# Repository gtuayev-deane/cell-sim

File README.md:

# Cell Simulator

This cell-sim is designed to mimic a LiPo battery pack for develpoment of the surrounding electronics, like a BMS.

- 16 channels
- Open-Source hardware design, you can embed onto your own HIL setup
- ⚡️ 0-4.5V and 0-500mA per channel
- DMM muxed to each channel for arbitarily precise measurment
- Open-circuit simulation on each channel
- 📏 16bit ADC feedback for voltage and current
- 🔌 USB w/ Python software interface (+ 100MBit Ethernet + WiFi waiting for firmware support)

## Design overview

## Getting Started

1. Install python if you don't have it already
2. Install the requirements `pip install -r requirements.txt`
3. Connect the board via USB

4. Power the board with the 12V input (supply: 1A minimum, 3A recommended)
5. Run the example python script `python example_set_voltages.py`
6. Voltages should be set to 3.5V, then rainbow from 1V to 4V across the 16 channels and current should be close to 0A.

You should see something like this:

## Notes
1. To get best low noise performance, use a quality power supply for the input supply.

## Firmware

### Update Firmware
We use PlatformIO to build and upload the firmware via USB.
1. Install PlatformIO: https://platformio.org/install
2. Connect the board via USB (might need to accept connection popup on Mac)
3. Run `pio run -t upload` or install the PlatformIO VSCode extension and use the upload button.

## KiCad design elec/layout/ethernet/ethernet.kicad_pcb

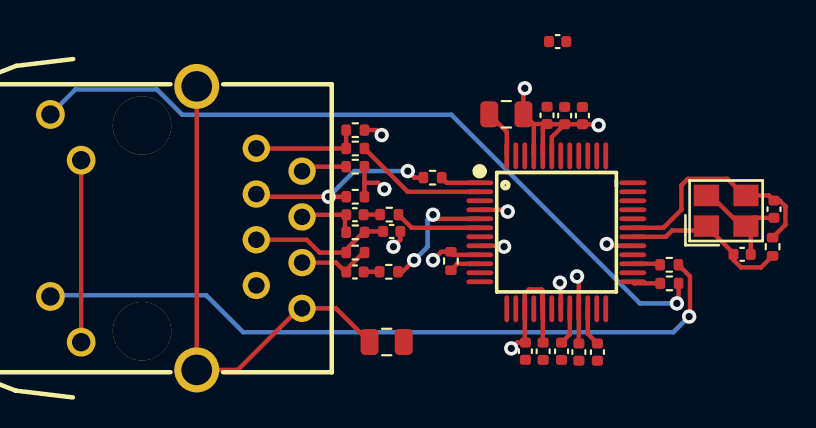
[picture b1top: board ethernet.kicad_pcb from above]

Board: 2 copper layers, 32 parts (0 on the bottom side), 27 nets.

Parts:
C1: 50V 1nF X7R ±10% 0805 Multilayer Ceramic Capacito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; C0805
C2: 50V 22nF X7R ±10% 0402 Multilayer Ceramic Capacit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; C0402
C3, C4: 50V 6.8nF X7R ±10% 0402 Multilayer Ceramic Capaci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; C0402
C5, C6: 50V 10nF X7R ±10% 0402 Multilayer Ceramic Capacit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; C0402
C7: 10V 4.7uF X5R ±20% 0402 Multilayer Ceramic Capaci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; C0402
C8, C9, C10, C11, C12, C13: 16V 100nF X7R ±10% 0402 Multilayer Ceramic Capaci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; C0402
C14: 25V 10uF X5R ±10% 0805 Multilayer Ceramic Capacit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; C0805
C15, C16: 50V 10pF C0G ±5% 0402 Multilayer Ceramic Capacito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; C0402
R1, R2: 62.5mW Thick Film Resistors 50V ±100ppm/℃ ±1% 200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; R0402
R3, R4, R8, R9: 62.5mW Thick Film Resistors 50V ±100ppm/℃ ±1% 33Ω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; R0402
R5, R6, R10, R11: 62.5mW Thick Film Resistors 50V ±100ppm/℃ ±1% 49.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; R0402
R7: 62.5mW Thick Film Resistors 50V ±1% ±200ppm/℃ 10Ω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; R0402
R12: 62.5mW Thick Film Resistors 50V ±100ppm/℃ ±1% 12.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; R0402
R13: 62.5mW Thick Film Resistors 50V ±100ppm/℃ ±1% 1MΩ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; R0402
U1: ?; LQFP-48_L7.0-W7.0-P0.50-LS9.0-BL
U2: ?; RJ45-TH_J1B1211CCD
U3: ?; CRYSTAL-SMD_4P-L3.2-W2.5-BL

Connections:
_1v2o: C6.1, U1.22
actled: R2.1, U1.27
cgnd: C1.1, U2.8, U2.13, U2.14
exres1: R12.1, U1.10
gnd-1: C1.2, C2.2, C5.2, C6.2, C7.2, C8.2, C9.2, C10.2, C11.2, C12.2, C13.2, C14.2, R12.2, U1.3, U1.9, U1.14, U1.16, U1.19, U1.29, U1.48
linkled: R1.1, U1.25
lled_minus: R1.2, U2.9
nc: U1.12, U1.13, U1.46, U1.47
oscillator-gnd: C15.2, C16.2, U3.2, U3.4
rct: C5.1, R10.2, R11.2, U2.5
rd_minus: C3.2, R10.1, U2.6
rd_plus: C4.2, R11.1, U2.4
rled_minus: R2.2, U2.11
rsvd: U1.23, U1.38, U1.39, U1.40, U1.41, U1.42
rx_minus_damping-vcc: C3.1, R8.2
rx_plus_damping-vcc: C4.1, R9.2
rxn: R8.1, U1.5
rxp: R9.1, U1.6
tct: C2.1, R7.2, U2.2
td_minus: R4.2, R6.2, U2.3
td_plus: R3.2, R5.2, U2.1
tocap: C7.1, U1.20
txn: R4.1, U1.1
txp: R3.1, U1.2
vcc: C8.1, C9.1, C10.1, C11.1, C12.1, C13.1, C14.1, R5.1, R6.1, R7.1, U1.4, U1.8, U1.11, U1.15, U1.17, U1.21, U1.28, U1.43, U1.44, U1.45, U2.10, U2.12
xi_slash_clkin: C15.1, R13.1, U1.30, U3.1
xo: C16.1, R13.2, U1.31, U3.3

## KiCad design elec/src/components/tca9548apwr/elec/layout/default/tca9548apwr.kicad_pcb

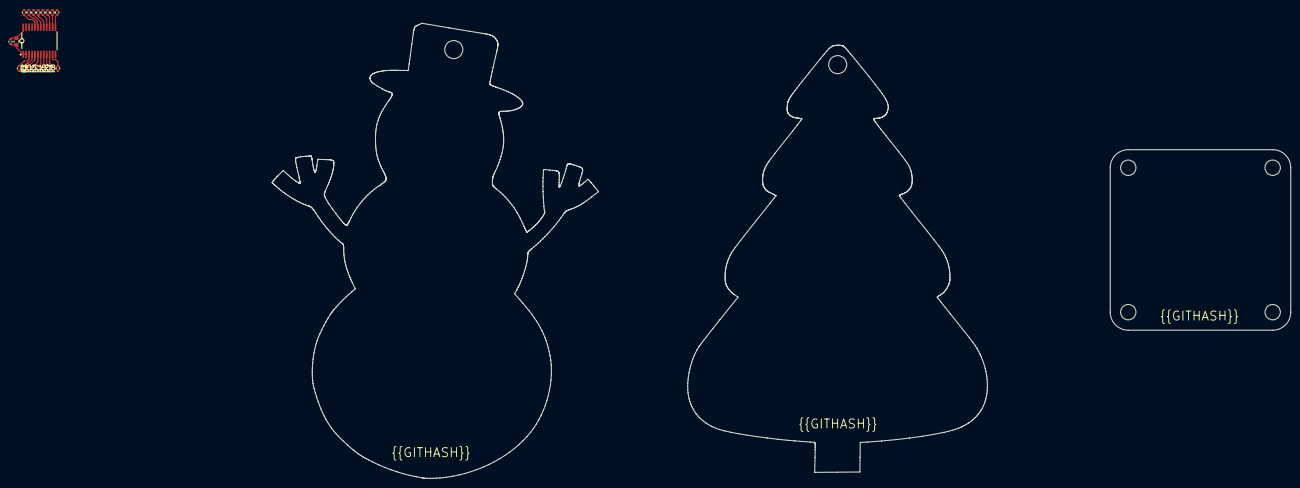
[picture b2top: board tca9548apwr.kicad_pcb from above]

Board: 2 copper layers, 20 parts (0 on the bottom side), 19 nets.

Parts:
C1: 16V 100nF X7R ±10% 0402 Multilayer Ceramic Capaci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; C0402
C2: 16V 2.2uF X5R ±10% 0603 Multilayer Ceramic Capaci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; C0603
R1, R2, R3, R4, R5, R6, R7, R8, R9, R10, R11, R12, R13, R14, R15, R16, R17: 62.5mW Thick Film Resistors 50V ±100ppm/℃ ±1% 10k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; R0402
U1: TSSOP-24_L7.8-W4.4-P0.65-LS6.4-BL

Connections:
ic-gnd: C1.2, C2.2, U1.1, U1.2, U1.12, U1.21
ic-scl: R2.2, U1.5
ic-scl-1: R4.2, U1.7
ic-scl-2: R6.2, U1.9
ic-scl-3: R8.2, U1.11
ic-scl-4: R10.2, U1.14
ic-scl-5: R12.2, U1.16
ic-scl-6: R14.2, U1.18
ic-scl-7: R16.2, U1.20
ic-sda: R3.2, U1.4
ic-sda-1: R5.2, U1.6
ic-sda-2: R7.2, U1.8
ic-sda-3: R9.2, U1.10
ic-sda-4: R11.2, U1.13
ic-sda-5: R13.2, U1.15
ic-sda-6: R15.2, U1.17
ic-sda-7: R17.2, U1.19
reset_: R1.1, U1.3
vcc: C1.1, C2.1, R1.2, R2.1, R3.1, R4.1, R5.1, R6.1, R7.1, R8.1, R9.1, R10.1, R11.1, R12.1, R13.1, R14.1, R15.1, R16.1, R17.1, U1.24

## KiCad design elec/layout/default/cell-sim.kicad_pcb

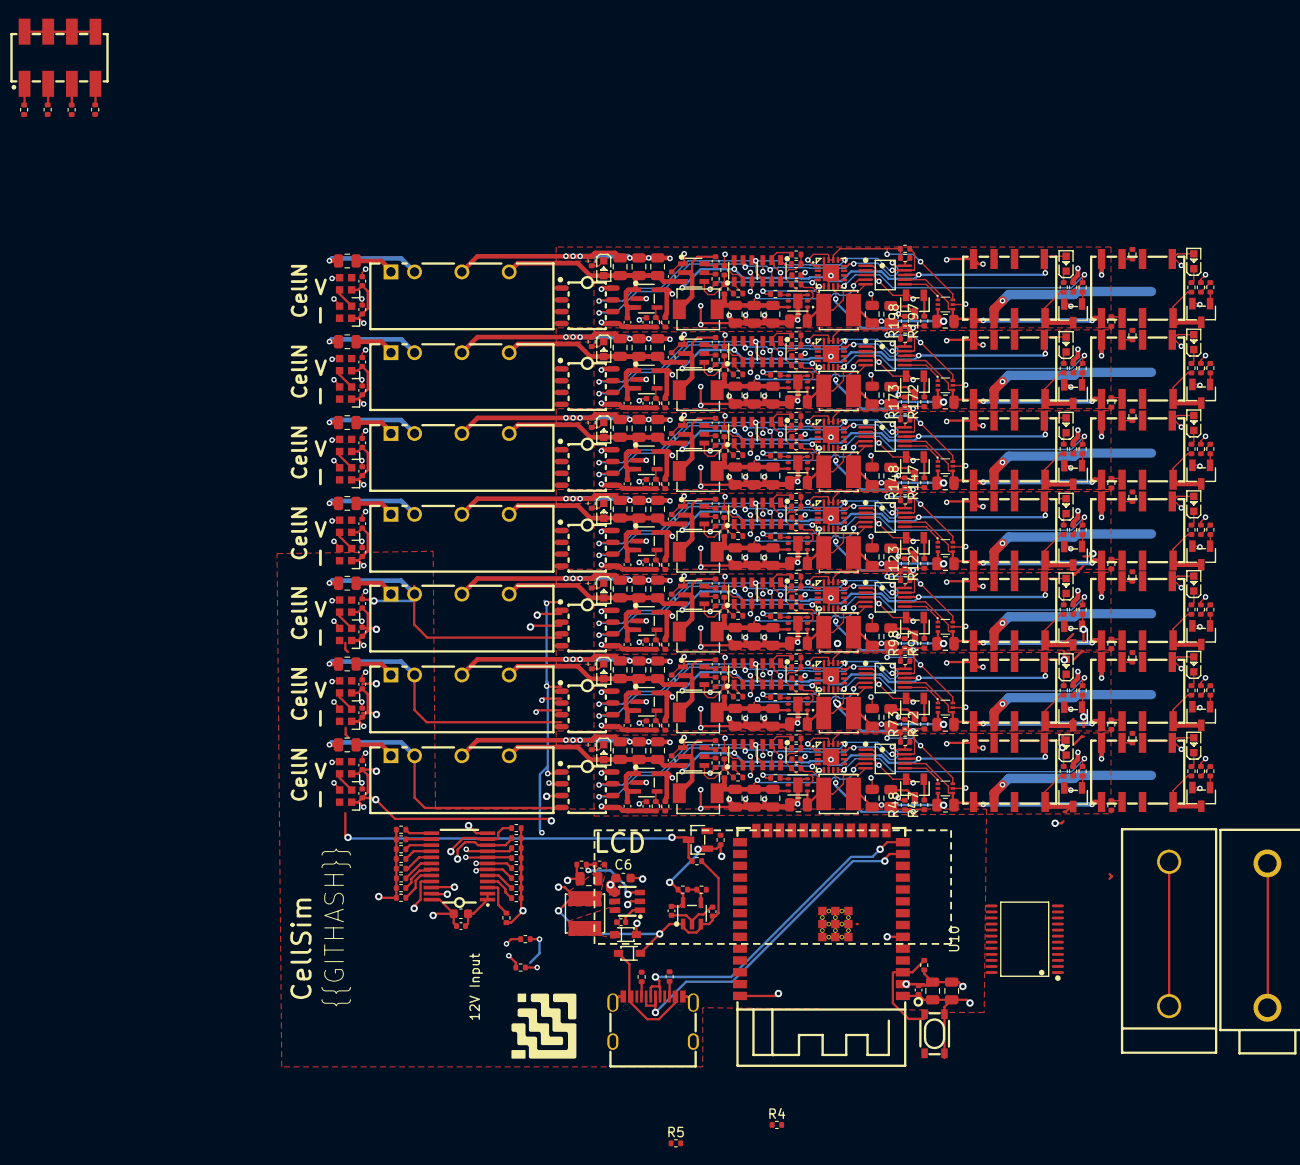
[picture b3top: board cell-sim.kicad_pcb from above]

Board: 4 copper layers, 499 parts (0 on the bottom side), 294 nets.

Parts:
C1, C4, C15, C19, C23, C24, C31, C35, C39, C40, C47, C51, C55, C56, C63, C67, C71, C72, C79, C83, C87, C88, C95, C99, C103, C104, C111, C115, C119, C120: 16V 100nF X7R ±10% 0402 Multilayer Ceramic Capaci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; C0402
C2, C3, C7, C12, C13, C14, C16, C17, C18, C21, C22, C28, C29, C30, C32, C33, C34, C37, C38, C44, C45, C46, C48, C49, C50, C53, C54, C60, C61, C62, C64, C65, C66, C69, C70, C76, C77, C78, C80, C81, C82, C85, C86, C92, C93, C94, C96, C97, C98, C101, C102, C108, C109, C110, C112, C113, C114, C117, C118: 25V 10uF X5R ±10% 0805 Multilayer Ceramic Capacit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; C0805
C5: 16V 2.2uF X5R ±10% 0603 Multilayer Ceramic Capaci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; C0603
C6: 16V 4.7uF X5R ±10% 0603 Multilayer Ceramic Capaci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; C0603
C8, C9, C10, C20, C25, C26, C36, C41, C42, C52, C57, C58, C68, C73, C74, C84, C89, C90, C100, C105, C106, C116, C121, C122: 25V 1uF X5R ±10% 0402 Multilayer Ceramic Capacito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; C0402
C11, C27, C43, C59, C75, C91, C107: 50V 2.2uF X5R ±10% 0805 Multilayer Ceramic Capaci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; C0805
DS1, DS2: ?; SOD-323_L1.8-W1.3-LS2.5-RD
L1, L3, L5, L7, L9, L11, L13, L15: ?; IND-SMD_L4.0-W4.0
L2, L4, L6, L8, L10, L12, L14: ?; IND-SMD_L4.4-W4.2
LED1, LED2, LED3, LED4, LED5, LED6, LED7, LED8, LED9, LED10, LED11, LED12, LED13, LED14, LED15, LED16, LED17, LED18, LED19, LED20, LED21: ?; LED0603-RD
Q1, Q2, Q3, Q4, Q5, Q6, Q7, Q8, Q9, Q10, Q11, Q12, Q13, Q14, Q15, Q16, Q17, Q18, Q19, Q20, Q21: ?; SOT-23-3_L2.9-W1.3-P1.90-LS2.4-BR
R1, R6, R7, R8, R9, R10, R11, R12, R13, R14, R15, R16, R17, R18, R19, R20, R21, R22, R29, R30, R34, R35, R38, R39, R42, R45, R48, R50, R51, R54, R55, R59, R60, R63, R64, R67, R70, R73, R75, R76, R79, R80, R84, R85, R88, R89, R92, R95, R98, R100, R101, R104, R105, R109, R110, R113, R114, R117, R120, R123, R125, R126, R129, R130, R134, R135, R138, R139, R142, R145, R148, R150, R151, R154, R155, R159, R160, R163, R164, R167, R170, R173, R175, R176, R179, R180, R184, R185, R188, R189, R192, R195, R198, R200, R201, R204, R205: 62.5mW Thick Film Resistors 50V ±100ppm/℃ ±1% 10k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; R0402
R2, R3: 62.5mW Thick Film Resistors 50V ±100ppm/℃ ±1% 4.7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; R0402
R4: 62.5mW Thick Film Resistors 50V ±100ppm/℃ ±1% 86.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; R0402
R5, R53, R78, R103, R128, R153, R178, R203: 62.5mW Thick Film Resistors 50V ±100ppm/℃ ±1% 6.2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; R0402
R23, R24: 62.5mW Thick Film Resistors 50V ±100ppm/℃ ±1% 2kΩ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; R0402
R25: 62.5mW Thick Film Resistors 50V ±1% ±200ppm/℃ 22.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; R0402
R26: 62.5mW Thick Film Resistors 50V ±100ppm/℃ ±1% 4.1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; R0402
R27: 62.5mW Thick Film Resistors 50V ±100ppm/℃ ±1% 17.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; R0402
R28: 62.5mW Thick Film Resistors 50V ±100ppm/℃ ±1% 10.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; R0402
R31, R56, R81, R106, R131, R156, R181: 62.5mW Thick Film Resistors 50V ±100ppm/℃ ±1% 14k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; R0402
R32, R57, R82, R107, R132, R157, R182: 62.5mW Thick Film Resistors 50V ±100ppm/℃ ±1% 24k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; R0402
R33, R58, R83, R108, R133, R158, R183: 62.5mW Thick Film Resistors 50V ±100ppm/℃ ±1% 37.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; R0402
R36, R61, R86, R111, R136, R161, R186: 62.5mW Thick Film Resistors 50V ±100ppm/℃ ±1% 43k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; R0402
R37, R62, R87, R112, R137, R162, R187: 62.5mW Thick Film Resistors 50V ±100ppm/℃ ±1% 60.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; R0402
R40, R65, R90, R115, R140, R165, R190: 125mW Thick Film Resistors 150V ±1% 100mΩ 0805 Ch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; R0805
R41, R44, R66, R69, R91, R94, R116, R119, R141, R144, R166, R169, R191, R194: 62.5mW Thick Film Resistors 50V ±100ppm/℃ ±1% 13k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; R0402
R43, R46, R47, R68, R71, R72, R93, R96, R97, R118, R121, R122, R143, R146, R147, R168, R171, R172, R193, R196, R197, R206, R207, R208, R209: 62.5mW Thick Film Resistors 50V ±100ppm/℃ ±1% 1kΩ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; R0402
R49, R74, R99, R124, R149, R174, R199: 125mW Thick Film Resistors 150V ±100ppm/℃ ±1% 226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; R0805
R52, R77, R102, R127, R152, R177, R202: 62.5mW Thick Film Resistors 50V ±100ppm/℃ ±1% 11.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; R0402
U1: ?; WIRELM-SMD_ESP32-S3-WROOM-1
U2: ?; KEY-SMD_4P-L4.2-W3.2-P2.20-LS4.6
U3: ?; USB-C-SMD_KH-TYPE-C-16P
U4: ?; AUDIO-TH_24.243.1
U5: ?; CONN-TH_24.243.2
U6: ?; TSSOP-24_L7.8-W4.4-P0.65-LS6.4-BL
U7: 0.6A, 42V, 1.1MHz Buck Regulator; SOT-23-6_L2.9-W1.6-P0.95-LS2.8-BR
U8, U24, U38, U52, U66, U80, U94, U108: ?; SOT-23-5_L3.0-W1.7-P0.95-LS2.8-BL
U9: ?; SOT-23-3_L2.9-W1.3-P1.90-LS2.4-BR
U10: ?; SSOP-24_L8.1-W5.3-P0.65-LS7.8-BL
U11, U25, U39, U53, U67, U81, U95: ?; PWRM-TH_BXXXXS-2WR2
U12, U26, U40, U54, U68, U82, U96: ?; MSOP-10_L3.0-W3.0-P0.50-LS5.0-BL
U13, U14, U15, U27, U28, U29, U41, U42, U43, U55, U56, U57, U69, U70, U71, U83, U84, U85, U97, U98, U99: ?; SOT-23-6_L2.9-W1.6-P0.95-LS2.8-BL
U16, U30, U44, U58, U72, U86, U100: ?; WSON-6_L2.0-W2.0-P0.65-TL-EP
U17, U31, U45, U59, U73, U87, U101: ?; SOT-563_L1.6-W1.2-P0.50-LS1.6-TL
U18, U19, U32, U33, U46, U47, U60, U61, U74, U75, U88, U89, U102, U103: ?; RELAY-SMD_HFD4-5-SR
U20, U34, U48, U62, U76, U90, U104: ?; QFN-16_L3.0-W3.0-P0.50-BL-EP1.7
U21, U35, U49, U63, U77, U91, U105: ?; SOIC-8_L4.9-W3.9-P1.27-LS6.0-TL
U22, U23, U36, U37, U50, U51, U64, U65, U78, U79, U92, U93, U106, U107: ?; LED-SMD_4P-L2.0-W2.0-BR
U109: ?; HDR-SMD_8P-P2.54-V-M-R2-C4-LS7.4

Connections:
_1: R206.2, U109.1
_3: R207.2, U109.3
_5: R208.2, U109.5
_7: R209.2, U109.7
buck.feedback_div-out: R25.2, R26.1, U7.3
buck.ic-sw: C8.2, DS1.1, L1.1, U7.6
cb: C8.1, U7.1
cc1: R2.1, U3.A5
cc2: R3.1, U3.B5
cell1-gnd-1: C22.1, C28.2, C29.2, C30.2, C31.2, C32.2, C33.2, C34.2, C36.2, C37.2, C38.2, C41.2, C42.2, L3.2, Q4.2, Q6.2, R40.1, R49.1, R56.2, R59.2, R63.2, R68.2, R73.2, R78.2, U17.3, U25.4, U26.1, U26.3, U27.2, U28.1, U29.2, U29.6, U30.3, U30.7, U31.2, U31.5, U32.4, U33.4, U34.6, U34.16, U34.17, U35.5, U38.2
cell1-led_data: U22.2, U37.4
cell1-scl: R51.1, U12.10, U13.5, U15.5, U20.12, U21.6
cell1-sda: R50.1, U12.9, U13.4, U15.4, U20.13, U21.7
cell1-vcc-1: C12.1, C13.1, C14.1, C15.1, C25.1, LED1.2, LED2.2, U11.6, U12.8, U13.6, U14.3, U18.1, U24.1, U24.3
cell1-vcc-2: C26.1, R50.2, R51.2, R52.1, U13.3, U15.3, U17.6, U20.1, U20.14, U20.15, U21.8, U24.5
cell1.adc-ain2: U12.6, U17.1
cell1.adc-vcc: C16.1, C17.1, C18.1, L2.2, R33.1, U12.4, U16.6
cell1.adc-vcc-1: C20.1, C21.1, L3.1, R37.1, U12.5, U16.1
cell1.adc-vcc-2: R40.2, U12.7, U17.4, U18.5, U19.5
cell1.buck-enable: R35.1, U20.4
cell1.buck.ctrl_resistor-vfb: R32.2, R33.2, R34.1, U14.4
cell1.buck.dac-vout: R32.1, U13.1
cell1.buck.regulator-en: R35.2, U14.5
cell1.buck.regulator-sw: C19.2, L2.1, U14.2
cell1.buck.regulator-vbst: C19.1, U14.6
cell1.dmm_relay-gnd: R55.1, U19.3
cell1.dmm_relay-vcc: R54.1, U19.6
cell1.dmm_relay.fet-gate: Q2.1, R45.2
cell1.dmm_relay.indicator_led.resistor-cathode: LED3.1, R44.1
cell1.dmm_relay.relay-gnd: Q2.3, R44.2, U19.8
cell1.gpio-p4: R47.1, R48.1, U20.7
cell1.internal_ldo.feedback_div-out: R52.2, R53.1, U24.4
cell1.isolated_converter.led.resistor-cathode: LED1.1, R31.1
cell1.ldo-enable: R39.1, U20.5
cell1.ldo.ctrl_resistor-fb: R36.2, R37.2, R38.1, U16.2
cell1.ldo.dac-vout: R36.1, U15.1
cell1.ldo.regulator-en: R39.2, U16.4
cell1.load_switch.fet-gate: Q3.1, R47.2
cell1.load_switch.fet-n: Q3.3, R49.2
cell1.output_relay-input: R42.1, R43.1, U20.8
cell1.output_relay.fet-gate: Q1.1, R42.2
cell1.output_relay.indicator_led.resistor-cathode: LED2.1, R41.1
cell1.output_relay.relay-gnd: Q1.3, R41.2, U18.8
cell1.voltage_led.ic-vcc: U22.4, U23.2
cell2-gnd-1: C38.1, C44.2, C45.2, C46.2, C47.2, C48.2, C49.2, C50.2, C52.2, C53.2, C54.2, C57.2, C58.2, L5.2, Q7.2, Q9.2, R65.1, R74.1, R81.2, R84.2, R88.2, R93.2, R98.2, R103.2, U31.3, U39.4, U40.1, U40.3, U41.2, U42.1, U43.2, U43.6, U44.3, U44.7, U45.2, U45.5, U46.4, U47.4, U48.6, U48.16, U48.17, U49.5, U52.2
cell2-led_data: U36.2, U51.4
cell2-scl: R76.1, U26.10, U27.5, U29.5, U34.12, U35.6
cell2-sda: R75.1, U26.9, U27.4, U29.4, U34.13, U35.7
cell2-vcc-1: C28.1, C29.1, C30.1, C31.1, C41.1, LED4.2, LED5.2, U25.6, U26.8, U27.6, U28.3, U32.1, U38.1, U38.3
cell2-vcc-2: C42.1, R75.2, R76.2, R77.1, U27.3, U29.3, U31.6, U34.1, U34.14, U34.15, U35.8, U38.5
cell2.adc-ain2: U26.6, U31.1
cell2.adc-vcc: C32.1, C33.1, C34.1, L4.2, R58.1, U26.4, U30.6
cell2.adc-vcc-1: C36.1, C37.1, L5.1, R62.1, U26.5, U30.1
cell2.adc-vcc-2: R65.2, U26.7, U31.4, U32.5, U33.5
cell2.buck-enable: R60.1, U34.4
cell2.buck.ctrl_resistor-vfb: R57.2, R58.2, R59.1, U28.4
cell2.buck.dac-vout: R57.1, U27.1
cell2.buck.regulator-en: R60.2, U28.5
cell2.buck.regulator-sw: C35.2, L4.1, U28.2
cell2.buck.regulator-vbst: C35.1, U28.6
cell2.dmm_relay-gnd: R80.1, U33.3
cell2.dmm_relay-vcc: R79.1, U33.6
cell2.dmm_relay.fet-gate: Q5.1, R70.2
cell2.dmm_relay.indicator_led.resistor-cathode: LED6.1, R69.1
cell2.dmm_relay.relay-gnd: Q5.3, R69.2, U33.8
cell2.gpio-p4: R72.1, R73.1, U34.7
cell2.internal_ldo.feedback_div-out: R77.2, R78.1, U38.4
cell2.isolated_converter.led.resistor-cathode: LED4.1, R56.1
cell2.ldo-enable: R64.1, U34.5
cell2.ldo.ctrl_resistor-fb: R61.2, R62.2, R63.1, U30.2
cell2.ldo.dac-vout: R61.1, U29.1
cell2.ldo.regulator-en: R64.2, U30.4
cell2.load_switch.fet-gate: Q6.1, R72.2
cell2.load_switch.fet-n: Q6.3, R74.2
cell2.output_relay-input: R67.1, R68.1, U34.8
cell2.output_relay.fet-gate: Q4.1, R67.2
cell2.output_relay.indicator_led.resistor-cathode: LED5.1, R66.1
cell2.output_relay.relay-gnd: Q4.3, R66.2, U32.8
cell2.voltage_led.ic-vcc: U36.4, U37.2
cell3-gnd-1: C54.1, C60.2, C61.2, C62.2, C63.2, C64.2, C65.2, C66.2, C68.2, C69.2, C70.2, C73.2, C74.2, L7.2, Q10.2, Q12.2, R90.1, R99.1, R106.2, R109.2, R113.2, R118.2, R123.2, R128.2, U45.3, U53.4, U54.1, U54.3, U55.2, U56.1, U57.2, U57.6, U58.3, U58.7, U59.2, U59.5, U60.4, U61.4, U62.6, U62.16, U62.17, U63.5, U66.2
cell3-led_data: U50.2, U65.4
cell3-scl: R101.1, U40.10, U41.5, U43.5, U48.12, U49.6
cell3-sda: R100.1, U40.9, U41.4, U43.4, U48.13, U49.7
cell3-vcc-1: C44.1, C45.1, C46.1, C47.1, C57.1, LED7.2, LED8.2, U39.6, U40.8, U41.6, U42.3, U46.1, U52.1, U52.3
cell3-vcc-2: C58.1, R100.2, R101.2, R102.1, U41.3, U43.3, U45.6, U48.1, U48.14, U48.15, U49.8, U52.5
cell3.adc-ain2: U40.6, U45.1
cell3.adc-vcc: C48.1, C49.1, C50.1, L6.2, R83.1, U40.4, U44.6
cell3.adc-vcc-1: C52.1, C53.1, L7.1, R87.1, U40.5, U44.1
cell3.adc-vcc-2: R90.2, U40.7, U45.4, U46.5, U47.5
cell3.buck-enable: R85.1, U48.4
cell3.buck.ctrl_resistor-vfb: R82.2, R83.2, R84.1, U42.4
cell3.buck.dac-vout: R82.1, U41.1
cell3.buck.regulator-en: R85.2, U42.5
cell3.buck.regulator-sw: C51.2, L6.1, U42.2
cell3.buck.regulator-vbst: C51.1, U42.6
cell3.dmm_relay-gnd: R105.1, U47.3
cell3.dmm_relay-vcc: R104.1, U47.6
cell3.dmm_relay.fet-gate: Q8.1, R95.2
cell3.dmm_relay.indicator_led.resistor-cathode: LED9.1, R94.1
cell3.dmm_relay.relay-gnd: Q8.3, R94.2, U47.8
cell3.gpio-p4: R97.1, R98.1, U48.7
cell3.internal_ldo.feedback_div-out: R102.2, R103.1, U52.4
cell3.isolated_converter.led.resistor-cathode: LED7.1, R81.1
cell3.ldo-enable: R89.1, U48.5
cell3.ldo.ctrl_resistor-fb: R86.2, R87.2, R88.1, U44.2
cell3.ldo.dac-vout: R86.1, U43.1
cell3.ldo.regulator-en: R89.2, U44.4
cell3.load_switch.fet-gate: Q9.1, R97.2
cell3.load_switch.fet-n: Q9.3, R99.2
cell3.output_relay-input: R92.1, R93.1, U48.8
cell3.output_relay.fet-gate: Q7.1, R92.2
cell3.output_relay.indicator_led.resistor-cathode: LED8.1, R91.1
cell3.output_relay.relay-gnd: Q7.3, R91.2, U46.8
cell3.voltage_led.ic-vcc: U50.4, U51.2
cell4-gnd-1: C70.1, C76.2, C77.2, C78.2, C79.2, C80.2, C81.2, C82.2, C84.2, C85.2, C86.2, C89.2, C90.2, L9.2, Q13.2, Q15.2, R115.1, R124.1, R131.2, R134.2, R138.2, R143.2, R148.2, R153.2, U59.3, U67.4, U68.1, U68.3, U69.2, U70.1, U71.2, U71.6, U72.3, U72.7, U73.2, U73.5, U74.4, U75.4, U76.6, U76.16, U76.17, U77.5, U80.2
cell4-led_data: U64.2, U79.4
cell4-scl: R126.1, U54.10, U55.5, U57.5, U62.12, U63.6
cell4-sda: R125.1, U54.9, U55.4, U57.4, U62.13, U63.7
cell4-vcc-1: C60.1, C61.1, C62.1, C63.1, C73.1, LED10.2, LED11.2, U53.6, U54.8, U55.6, U56.3, U60.1, U66.1, U66.3
cell4-vcc-2: C74.1, R125.2, R126.2, R127.1, U55.3, U57.3, U59.6, U62.1, U62.14, U62.15, U63.8, U66.5
cell4.adc-ain2: U54.6, U59.1
cell4.adc-vcc: C64.1, C65.1, C66.1, L8.2, R108.1, U54.4, U58.6
cell4.adc-vcc-1: C68.1, C69.1, L9.1, R112.1, U54.5, U58.1
cell4.adc-vcc-2: R115.2, U54.7, U59.4, U60.5, U61.5
cell4.buck-enable: R110.1, U62.4
cell4.buck.ctrl_resistor-vfb: R107.2, R108.2, R109.1, U56.4
cell4.buck.dac-vout: R107.1, U55.1
cell4.buck.regulator-en: R110.2, U56.5
cell4.buck.regulator-sw: C67.2, L8.1, U56.2
cell4.buck.regulator-vbst: C67.1, U56.6
cell4.dmm_relay-gnd: R130.1, U61.3
cell4.dmm_relay-vcc: R129.1, U61.6
cell4.dmm_relay.fet-gate: Q11.1, R120.2
cell4.dmm_relay.indicator_led.resistor-cathode: LED12.1, R119.1
cell4.dmm_relay.relay-gnd: Q11.3, R119.2, U61.8
cell4.gpio-p4: R122.1, R123.1, U62.7
cell4.internal_ldo.feedback_div-out: R127.2, R128.1, U66.4
cell4.isolated_converter.led.resistor-cathode: LED10.1, R106.1
cell4.ldo-enable: R114.1, U62.5
cell4.ldo.ctrl_resistor-fb: R111.2, R112.2, R113.1, U58.2
cell4.ldo.dac-vout: R111.1, U57.1
cell4.ldo.regulator-en: R114.2, U58.4
cell4.load_switch.fet-gate: Q12.1, R122.2
cell4.load_switch.fet-n: Q12.3, R124.2
cell4.output_relay-input: R117.1, R118.1, U62.8
cell4.output_relay.fet-gate: Q10.1, R117.2
cell4.output_relay.indicator_led.resistor-cathode: LED11.1, R116.1
cell4.output_relay.relay-gnd: Q10.3, R116.2, U60.8
cell4.voltage_led.ic-vcc: U64.4, U65.2
cell5-gnd-1: C86.1, C92.2, C93.2, C94.2, C95.2, C96.2, C97.2, C98.2, C100.2, C101.2, C102.2, C105.2, C106.2, L11.2, Q16.2, Q18.2, R140.1, R149.1, R156.2, R159.2, R163.2, R168.2, R173.2, R178.2, U73.3, U81.4, U82.1, U82.3, U83.2, U84.1, U85.2, U85.6, U86.3, U86.7, U87.2, U87.5, U88.4, U89.4, U90.6, U90.16, U90.17, U91.5, U94.2
cell5-led_data: U78.2, U93.4
cell5-scl: R151.1, U68.10, U69.5, U71.5, U76.12, U77.6
cell5-sda: R150.1, U68.9, U69.4, U71.4, U76.13, U77.7
cell5-vcc-1: C76.1, C77.1, C78.1, C79.1, C89.1, LED13.2, LED14.2, U67.6, U68.8, U69.6, U70.3, U74.1, U80.1, U80.3
cell5-vcc-2: C90.1, R150.2, R151.2, R152.1, U69.3, U71.3, U73.6, U76.1, U76.14, U76.15, U77.8, U80.5
cell5.adc-ain2: U68.6, U73.1
cell5.adc-vcc: C80.1, C81.1, C82.1, L10.2, R133.1, U68.4, U72.6
cell5.adc-vcc-1: C84.1, C85.1, L11.1, R137.1, U68.5, U72.1
cell5.adc-vcc-2: R140.2, U68.7, U73.4, U74.5, U75.5
cell5.buck-enable: R135.1, U76.4
cell5.buck.ctrl_resistor-vfb: R132.2, R133.2, R134.1, U70.4
cell5.buck.dac-vout: R132.1, U69.1
cell5.buck.regulator-en: R135.2, U70.5
cell5.buck.regulator-sw: C83.2, L10.1, U70.2
cell5.buck.regulator-vbst: C83.1, U70.6
cell5.dmm_relay-gnd: R155.1, U75.3
cell5.dmm_relay-vcc: R154.1, U75.6
cell5.dmm_relay.fet-gate: Q14.1, R145.2
cell5.dmm_relay.indicator_led.resistor-cathode: LED15.1, R144.1
cell5.dmm_relay.relay-gnd: Q14.3, R144.2, U75.8
cell5.gpio-p4: R147.1, R148.1, U76.7
cell5.internal_ldo.feedback_div-out: R152.2, R153.1, U80.4
cell5.isolated_converter.led.resistor-cathode: LED13.1, R131.1
cell5.ldo-enable: R139.1, U76.5
cell5.ldo.ctrl_resistor-fb: R136.2, R137.2, R138.1, U72.2
cell5.ldo.dac-vout: R136.1, U71.1
cell5.ldo.regulator-en: R139.2, U72.4
cell5.load_switch.fet-gate: Q15.1, R147.2
cell5.load_switch.fet-n: Q15.3, R149.2
cell5.output_relay-input: R142.1, R143.1, U76.8
cell5.output_relay.fet-gate: Q13.1, R142.2
cell5.output_relay.indicator_led.resistor-cathode: LED14.1, R141.1
cell5.output_relay.relay-gnd: Q13.3, R141.2, U74.8
cell5.voltage_led.ic-vcc: U78.4, U79.2
cell6-gnd-1: C102.1, C108.2, C109.2, C110.2, C111.2, C112.2, C113.2, C114.2, C116.2, C117.2, C118.2, C121.2, C122.2, L13.2, Q19.2, Q21.2, R165.1, R174.1, R181.2, R184.2, R188.2, R193.2, R198.2, R203.2, U87.3, U95.4, U96.1, U96.3, U97.2, U98.1, U99.2, U99.6, U100.3, U100.7, U101.2, U101.5, U102.4, U103.4, U104.6, U104.16, U104.17, U105.5, U108.2
cell6-led_data: U92.2, U107.4
cell6-scl: R176.1, U82.10, U83.5, U85.5, U90.12, U91.6
cell6-sda: R175.1, U82.9, U83.4, U85.4, U90.13, U91.7
cell6-vcc-1: C92.1, C93.1, C94.1, C95.1, C105.1, LED16.2, LED17.2, U81.6, U82.8, U83.6, U84.3, U88.1, U94.1, U94.3
cell6-vcc-2: C106.1, R175.2, R176.2, R177.1, U83.3, U85.3, U87.6, U90.1, U90.14, U90.15, U91.8, U94.5
cell6.adc-ain2: U82.6, U87.1
cell6.adc-vcc: C96.1, C97.1, C98.1, L12.2, R158.1, U82.4, U86.6
cell6.adc-vcc-1: C100.1, C101.1, L13.1, R162.1, U82.5, U86.1
cell6.adc-vcc-2: R165.2, U82.7, U87.4, U88.5, U89.5
cell6.buck-enable: R160.1, U90.4
cell6.buck.ctrl_resistor-vfb: R157.2, R158.2, R159.1, U84.4
cell6.buck.dac-vout: R157.1, U83.1
cell6.buck.regulator-en: R160.2, U84.5
cell6.buck.regulator-sw: C99.2, L12.1, U84.2
cell6.buck.regulator-vbst: C99.1, U84.6
cell6.dmm_relay-gnd: R180.1, U89.3
cell6.dmm_relay-vcc: R179.1, U89.6
cell6.dmm_relay.fet-gate: Q17.1, R170.2
cell6.dmm_relay.indicator_led.resistor-cathode: LED18.1, R169.1
cell6.dmm_relay.relay-gnd: Q17.3, R169.2, U89.8
cell6.gpio-p4: R172.1, R173.1, U90.7
cell6.internal_ldo.feedback_div-out: R177.2, R178.1, U94.4
cell6.isolated_converter.led.resistor-cathode: LED16.1, R156.1
cell6.ldo-enable: R164.1, U90.5
cell6.ldo.ctrl_resistor-fb: R161.2, R162.2, R163.1, U86.2
cell6.ldo.dac-vout: R161.1, U85.1
cell6.ldo.regulator-en: R164.2, U86.4
cell6.load_switch.fet-gate: Q18.1, R172.2
cell6.load_switch.fet-n: Q18.3, R174.2
cell6.output_relay-input: R167.1, R168.1, U90.8
cell6.output_relay.fet-gate: Q16.1, R167.2
cell6.output_relay.indicator_led.resistor-cathode: LED17.1, R166.1
cell6.output_relay.relay-gnd: Q16.3, R166.2, U88.8
cell6.voltage_led.ic-vcc: U92.4, U93.2
cell7-scl: R201.1, U96.10, U97.5, U99.5, U104.12, U105.6
cell7-sda: R200.1, U96.9, U97.4, U99.4, U104.13, U105.7
cell7-vcc-1: C118.1, L15.2, R190.1, R199.1, U101.3
cell7-vcc-2: C108.1, C109.1, C110.1, C111.1, C121.1, LED19.2, LED20.2, U95.6, U96.8, U97.6, U98.3, U102.1, U108.1, U108.3
cell7-vcc-3: C122.1, R200.2, R201.2, R202.1, U97.3, U99.3, U101.6, U104.1, U104.14, U104.15, U105.8, U108.5
cell7.adc-ain2: U96.6, U101.1
cell7.adc-vcc: C112.1, C113.1, C114.1, L14.2, R183.1, U96.4, U100.6
cell7.adc-vcc-1: C116.1, C117.1, L15.1, R187.1, U96.5, U100.1
cell7.adc-vcc-2: R190.2, U96.7, U101.4, U102.5, U103.5
cell7.buck-enable: R185.1, U104.4
cell7.buck.ctrl_resistor-vfb: R182.2, R183.2, R184.1, U98.4
cell7.buck.dac-vout: R182.1, U97.1
cell7.buck.regulator-en: R185.2, U98.5
cell7.buck.regulator-sw: C115.2, L14.1, U98.2
cell7.buck.regulator-vbst: C115.1, U98.6
cell7.dmm_relay-gnd: R205.1, U103.3
cell7.dmm_relay-vcc: R204.1, U103.6
cell7.dmm_relay.fet-gate: Q20.1, R195.2
cell7.dmm_relay.indicator_led.resistor-cathode: LED21.1, R194.1
cell7.dmm_relay.relay-gnd: Q20.3, R194.2, U103.8
cell7.gpio-p4: R197.1, R198.1, U104.7
cell7.internal_ldo.feedback_div-out: R202.2, R203.1, U108.4
cell7.isolated_converter.led.resistor-cathode: LED19.1, R181.1
cell7.ldo-enable: R189.1, U104.5
cell7.ldo.ctrl_resistor-fb: R186.2, R187.2, R188.1, U100.2
cell7.ldo.dac-vout: R186.1, U99.1
cell7.ldo.regulator-en: R189.2, U100.4
cell7.load_switch.fet-gate: Q21.1, R197.2
cell7.load_switch.fet-n: Q21.3, R199.2
cell7.output_relay-input: R192.1, R193.1, U104.8
cell7.output_relay.fet-gate: Q19.1, R192.2
cell7.output_relay.indicator_led.resistor-cathode: LED20.1, R191.1
cell7.output_relay.relay-gnd: Q19.3, R191.2, U102.8
cell7.voltage_led.ic-vcc: U106.4, U107.2
ch4: R145.1, R146.1, U10.5
ch5: R170.1, R171.1, U10.4
ch6: R195.1, R196.1, U10.3
dm: U1.13, U3.A7, U3.B7
dp: U1.14, U3.A6, U3.B6
gnd: C1.2, C2.2, C3.2, C4.2, C5.2, C6.2, C7.2, C9.2, C10.2, C11.2, C12.2, C13.2, C14.2, C15.2, C16.2, C17.2, C18.2, C20.2, C21.2, C22.2, C23.2, C24.2, C25.2, C26.2, C27.2, C39.2, C40.2, C43.2, C55.2, C56.2, C59.2, C71.2, C72.2, C75.2, C87.2, C88.2, C91.2, C103.2, C104.2, C107.2, C119.2, C120.2, DS1.2, Q1.2, Q2.2, Q3.2, Q5.2, Q8.2, Q11.2, Q14.2, Q17.2, Q20.2, R2.2, R3.2, R5.2, R26.2, R28.2, R31.2, R34.2, R38.2, R43.2, R46.2, R48.2, R53.2, R71.2, R96.2, R121.2, R146.2, R171.2, R196.2, U1.1, U1.40, U1.41, U2.3, U2.4, U3.1, U3.2, U3.3, U3.4, U3.A1, U3.A12, U3.B1, U3.B12, U6.1, U6.2, U6.12, U6.21, U7.2, U8.2, U10.12, U11.2, U11.4, U12.1, U12.3, U13.2, U14.1, U15.2, U15.6, U16.3, U16.7, U17.2, U17.5, U18.4, U19.4, U20.6, U20.16, U20.17, U21.4, U21.5, U22.3, U23.3, U24.2, U25.2, U35.4, U36.3, U37.3, U39.2, U49.4, U50.3, U51.3, U53.2, U63.4, U64.3, U65.3, U67.2, U77.4, U78.3, U79.3, U81.2, U91.4, U92.3, U93.3, U95.2, U105.4, U106.3, U107.3, U109.2, U109.4, U109.6, U109.8
gnd-2: R55.2, R80.2, R105.2, R130.2, R155.2, R180.2, R205.2, U5.1, U5.2
hv_signal: R30.2, U9.3, U23.4
io1: R45.1, R46.1, U1.39, U10.9
io2: R70.1, R71.1, U1.38, U10.8
io3: R95.1, R96.1, U1.15, U10.7
io4: R120.1, R121.1, U1.4, U10.6
io5: U1.5, U10.15
io15: R29.2, U1.8, U9.2
ldo3v3.feedback_div-out: R27.2, R28.1, U8.4
micro.ic-en: R1.2, U1.3, U2.1, U2.2
micro.ic-scl: R24.1, R206.1, U1.6, U6.22
micro.ic-sda: R23.1, R207.1, U1.7, U6.23
micro.ic-vcc: R4.2, R5.1, U1.9
mux.ic-scl: R7.2, U6.5
mux.ic-scl-1: R9.2, U6.7, U21.3
mux.ic-scl-2: R11.2, U6.9, U35.3
mux.ic-scl-3: R13.2, U6.11, U49.3
mux.ic-scl-4: R15.2, U6.14, U63.3
mux.ic-scl-5: R17.2, U6.16, U77.3
mux.ic-scl-6: R19.2, U6.18, U91.3
mux.ic-scl-7: R21.2, U6.20, U105.3
mux.ic-sda: R8.2, U6.4
mux.ic-sda-1: R10.2, U6.6, U21.2
mux.ic-sda-2: R12.2, U6.8, U35.2
mux.ic-sda-3: R14.2, U6.10, U49.2
mux.ic-sda-4: R16.2, U6.13, U63.2
mux.ic-sda-5: R18.2, U6.15, U77.2
mux.ic-sda-6: R20.2, U6.17, U91.2
mux.ic-sda-7: R22.2, U6.19, U105.2
reset_: R6.1, U6.3
usbc-vcc: DS2.2, U3.A4, U3.A9, U3.B4, U3.B9
vcc: C6.1, C11.1, C27.1, C43.1, C59.1, C75.1, C91.1, C107.1, R4.1, U7.4, U7.5, U11.1, U25.1, U39.1, U53.1, U67.1, U81.1, U95.1
vcc-2: C7.1, C9.1, C23.1, C24.1, C39.1, C40.1, C55.1, C56.1, C71.1, C72.1, C87.1, C88.1, C103.1, C104.1, C119.1, C120.1, DS2.1, L1.2, LED3.2, LED6.2, LED9.2, LED12.2, LED15.2, LED18.2, LED21.2, R25.1, R30.1, R208.1, U8.1, U8.3, U19.1, U22.1, U23.1, U33.1, U36.1, U37.1, U47.1, U50.1, U51.1, U61.1, U64.1, U65.1, U75.1, U78.1, U79.1, U89.1, U92.1, U93.1, U103.1, U106.1, U107.1
vcc-3: C1.1, C2.1, C3.1, C4.1, C5.1, C10.1, R1.1, R6.2, R7.1, R8.1, R9.1, R10.1, R11.1, R12.1, R13.1, R14.1, R15.1, R16.1, R17.1, R18.1, R19.1, R20.1, R21.1, R22.1, R23.2, R24.2, R27.1, R29.1, R209.1, U1.2, U6.24, U8.5, U9.1, U10.24, U21.1, U35.1, U49.1, U63.1, U77.1, U91.1, U105.1
vcc-4: R54.2, R79.2, R104.2, R129.2, R154.2, R179.2, R204.2, U4.1, U4.2

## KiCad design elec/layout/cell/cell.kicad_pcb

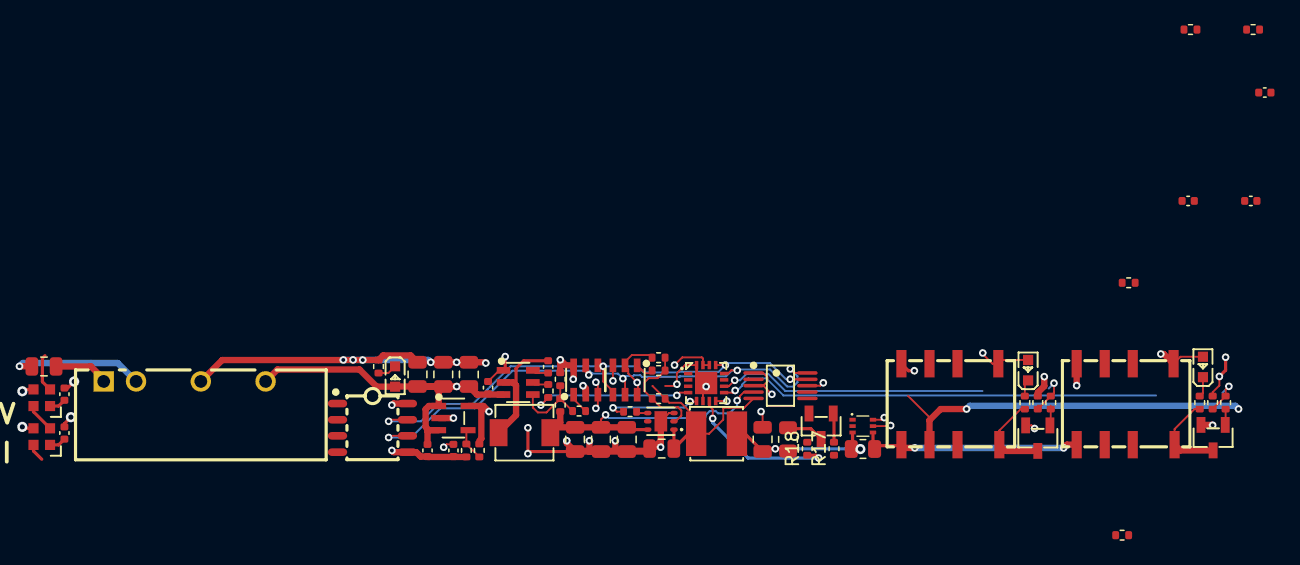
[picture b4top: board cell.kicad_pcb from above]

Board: 4 copper layers, 65 parts (0 on the bottom side), 41 nets.

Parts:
C1: 50V 2.2uF X5R ±10% 0805 Multilayer Ceramic Capaci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; C0805
C2, C3, C4, C6, C7, C8, C13, C14: 25V 10uF X5R ±10% 0805 Multilayer Ceramic Capacit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; C0805
C5, C9, C11, C15, C16: 16V 100nF X7R ±10% 0402 Multilayer Ceramic Capaci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; C0402
C10, C17, C18: 25V 1uF X5R ±10% 0402 Multilayer Ceramic Capacito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; C0402
C12: 50V 10nF X7R ±10% 0402 Multilayer Ceramic Capacit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; C0402
L1: ?; IND-SMD_L4.4-W4.2
L2: ?; IND-SMD_L4.0-W4.0
LED1, LED2, LED3: ?; LED0603-RD
Q1, Q2, Q3: ?; SOT-23-3_L2.9-W1.3-P1.90-LS2.4-BR
R1: 62.5mW Thick Film Resistors 50V ±100ppm/℃ ±1% 14k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; R0402
R2: 62.5mW Thick Film Resistors 50V ±100ppm/℃ ±1% 24k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; R0402
R3: 62.5mW Thick Film Resistors 50V ±100ppm/℃ ±1% 37.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; R0402
R4, R5, R8, R9, R12, R15, R18, R20, R21, R24, R25: 62.5mW Thick Film Resistors 50V ±100ppm/℃ ±1% 10k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; R0402
R6: 62.5mW Thick Film Resistors 50V ±100ppm/℃ ±1% 43k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; R0402
R7: 62.5mW Thick Film Resistors 50V ±100ppm/℃ ±1% 60.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; R0402
R10: 125mW Thick Film Resistors 150V ±1% 100mΩ 0805 Ch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; R0805
R11, R14: 62.5mW Thick Film Resistors 50V ±100ppm/℃ ±1% 13k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; R0402
R13, R16, R17: 62.5mW Thick Film Resistors 50V ±100ppm/℃ ±1% 1kΩ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; R0402
R19: 125mW Thick Film Resistors 150V ±100ppm/℃ ±1% 226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; R0805
R22: 62.5mW Thick Film Resistors 50V ±100ppm/℃ ±1% 11.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; R0402
R23: 62.5mW Thick Film Resistors 50V ±100ppm/℃ ±1% 6.2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; R0402
U1: ?; PWRM-TH_BXXXXS-2WR2
U2: ?; MSOP-10_L3.0-W3.0-P0.50-LS5.0-BL
U3, U4, U5: ?; SOT-23-6_L2.9-W1.6-P0.95-LS2.8-BL
U6: ?; WSON-6_L2.0-W2.0-P0.65-TL-EP
U7: ?; SOT-563_L1.6-W1.2-P0.50-LS1.6-TL
U8, U9: ?; RELAY-SMD_HFD4-5-SR
U10: ?; QFN-16_L3.0-W3.0-P0.50-BL-EP1.7
U11: ?; SOIC-8_L4.9-W3.9-P1.27-LS6.0-TL
U12, U13: ?; LED-SMD_4P-L2.0-W2.0-BR
U14: ?; SOT-23-5_L3.0-W1.7-P0.95-LS2.8-BL

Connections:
adc-vcc: C6.1, C7.1, C8.1, L1.2, R3.1, U2.4, U6.6
adc-vcc-1: C10.1, C11.1, C12.1, C13.1, L2.1, R7.1, U2.5, U6.1
ain3: U2.7, U7.1
buck-enable: R5.1, U10.4
buck.dac-vout: R2.1, U3.1
buck.regulator-en: R5.2, U4.5
current_sense.sensor-vcc: R10.2, U7.4, U8.5, U9.5
dmm_relay-gnd: R25.1, U9.3
dmm_relay-vcc: R24.1, U9.6
dmm_relay.fet-gate: Q2.1, R15.2
dmm_relay.indicator_led.resistor-cathode: LED3.1, R14.1
dmm_relay.relay-gnd: Q2.3, R14.2, U9.8
dmm_relay_enable: R15.1, R16.1, U10.9
fb: R6.2, R7.2, R8.1, U6.2
gnd: C1.2, U1.2
gnd-2: C15.2, C16.2, Q2.2, R16.2, U12.3, U13.3
gnd-6: C2.2, C3.2, C4.2, C5.2, C6.2, C7.2, C8.2, C10.2, C11.2, C12.2, C13.2, C14.2, C17.2, C18.2, Q1.2, Q3.2, R1.2, R4.2, R8.2, R13.2, R18.2, R23.2, U1.4, U2.1, U2.3, U3.2, U4.1, U5.2, U5.6, U6.3, U6.7, U7.2, U7.5, U8.4, U9.4, U10.6, U10.16, U10.17, U11.5, U14.2
input: R12.1, R13.1, U10.8
isolated_converter.led.resistor-cathode: LED1.1, R1.1
ldo-enable: R9.1, U10.5
ldo.dac-vout: R6.1, U5.1
ldo.regulator-en: R9.2, U6.4
load_switch.fet-gate: Q3.1, R17.2
n: Q3.3, R19.2
out: R22.2, R23.1, U14.4
output_relay.fet-gate: Q1.1, R12.2
output_relay.indicator_led.resistor-cathode: LED2.1, R11.1
output_relay.relay-gnd: Q1.3, R11.2, U8.8
p4: R17.1, R18.1, U10.7
scl-1: R21.1, U2.10, U3.5, U5.5, U10.12, U11.6
sda-1: R20.1, U2.9, U3.4, U5.4, U10.13, U11.7
sw: C9.2, L1.1, U4.2
vbst: C9.1, U4.6
vcc: C1.1, U1.1
vcc-1: U2.6, U8.6
vcc-2: C15.1, C16.1, LED3.2, U9.1, U12.1, U13.1
vcc-5: C14.1, L2.2, R10.1, R19.1, U7.3
vcc-6: C2.1, C3.1, C4.1, C5.1, C17.1, LED1.2, LED2.2, U1.6, U2.8, U3.6, U4.3, U8.1, U14.1, U14.3
vcc-7: C18.1, R20.2, R21.2, R22.1, U3.3, U5.3, U7.6, U10.1, U10.14, U10.15, U11.8, U14.5
vfb: R2.2, R3.2, R4.1, U4.4
voltage_led.ic-vcc: U12.4, U13.2

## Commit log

2024-07-25 Configure project
2024-08-08 transfer
2024-08-09 fix imports
2024-08-09 updated imports
2024-11-06 add limits and calibration points
2024-11-06 add leds
2024-11-06 cleanup net names
2024-11-06 create mux part
2024-11-06 comment out overrides
2024-11-07 add library parts
2024-11-12 use linked modules, remove local cache
2024-11-12 update i2c pins
2024-11-12 update layout
2024-11-13 add VSH connector
2024-11-13 added ethernet
2024-11-13 cleanup net naming and routing
2024-11-13 add components to thermistor simulator
2024-11-13 Add thermistor connections to Molex VSH + finish layout
2024-11-13 do not lick
2024-11-19 docs
2024-11-30 connect ethernet gnd to main gnd and update layout
2024-12-03 Update i2c pinouts
2024-12-03 fix pinouts, cleanup main example
2024-12-04 Fix layout merge issue
2024-12-04 Config mux to git rid of chatter, add print for Serial terminal
    Abstract out wire interface, no all 16 cells are functional
    Patch to increase NUM_LEDS now that all cells are enabled
    Update LDO and Buck DACs to use appropriate wire as well
2024-12-23 Fix SchottkyDiode spelling
2025-02-03 basic serial coms working
2025-02-03 update docs, cleanup examples
2025-02-03 docs tweaks
2025-02-04 add load switch + output relay support + dmm enable/disable
2025-02-04 auto-port finding
2025-02-25 Added self calibration routine on boot
2025-04-17 move example python script
2025-04-17 add poetry
2025-04-17 test script
